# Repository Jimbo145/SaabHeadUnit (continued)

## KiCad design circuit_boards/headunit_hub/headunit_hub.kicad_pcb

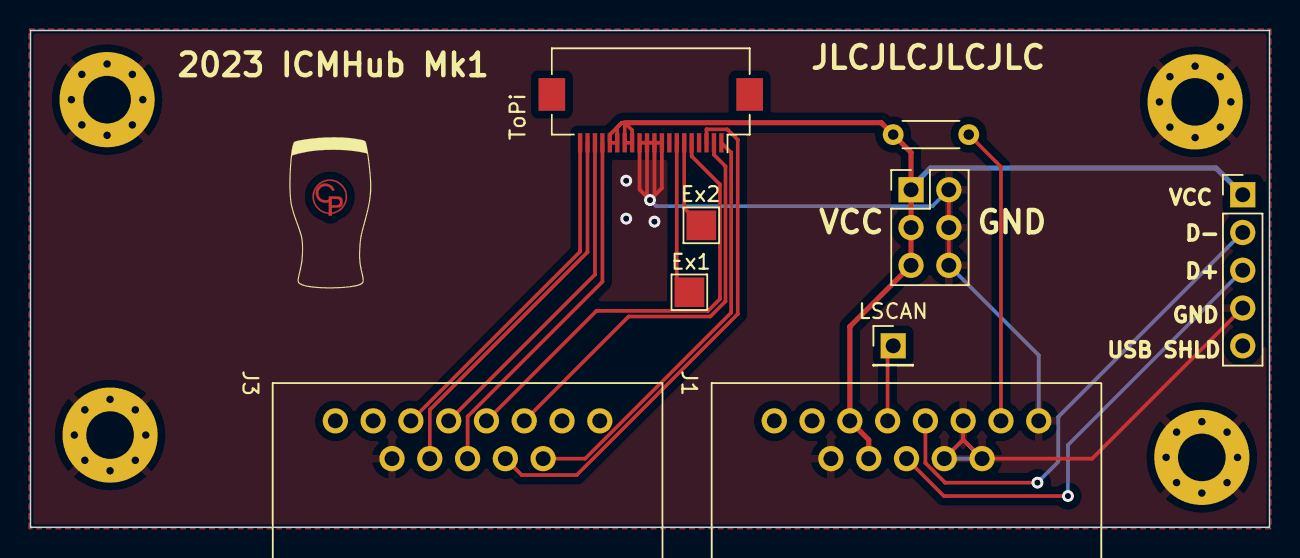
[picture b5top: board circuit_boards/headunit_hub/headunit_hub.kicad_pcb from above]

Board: 2 copper layers, 83.3 x 33.4 mm, 14 parts (0 on the bottom side), 16 nets.

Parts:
Ex1, Ex2: Conn_01x01_Pin; TestPoint_Pad_2.0x2.0mm
H1, H2, H4, H5: MountingHole_Pad; MountingHole_3.2mm_M3_Pad_Via
H3: Logo; CPlogo2(50)
J1, J3: 8P8C_LED_Shielded; rj45breakout
J5: USB_A; PinHeader_1x05_P2.54mm_Vertical
J6: Conn_02x03_Odd_Even; PinHeader_2x03_P2.54mm_Vertical
LSCAN: LSCAN; PinHeader_1x01_P2.54mm_Vertical
R1: R; R_Axial_DIN0204_L3.6mm_D1.6mm_P5.08mm_Horizontal
ToPi: Conn_01x20; Hirose_FH12-20S-0.5SH_1x20-1MP_P0.50mm_Horizontal

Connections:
/LSCAN: J1.6, LSCAN.1
/R_to_ActiveLED: J1.10, R1.2
AMFM_button: J3.1, ToPi.1
CD_button: J3.3, ToPi.3
Expansion_4: J3.8, ToPi.20
Expansion_5: J3.7, ToPi.19
Expansion_6: J3.6, ToPi.18
Expansion_7: J3.5, ToPi.17
GND: H1.1, H2.1, H4.1, H5.1, J1.1, J1.2, J1.3, J1.9, J1.SH, J3.SH, J5.4 (GND), J6.2, J6.4, J6.6, ToPi.9, ToPi.10, ToPi.11, ToPi.12
unnamed: Ex1.1, ToPi.7
unnamed: Ex2.1, ToPi.6
unnamed: J1.5, J5.3 (D+)
unnamed: J1.4, J5.2 (D-)
SCAN_button: J3.2, ToPi.2
Scrn_Brightness: J3.4, ToPi.5
VCC: J1.7, J1.8, J5.1 (VBUS), J6.1, J6.3, J6.5, R1.1, ToPi.13, ToPi.14, ToPi.15, ToPi.16

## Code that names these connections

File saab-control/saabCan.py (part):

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class GPIOManager:
    def __init__(self):
        self.pin_mapping = {
            'AMFM': gpiozero.DigitalOutputDevice(pin= 'GPIO26', active_high=True, initial_value=False),
            'SCAN': gpiozero.DigitalOutputDevice(pin= 'GPIO21', active_high=True, initial_value=False),
            'CD': gpiozero.DigitalOutputDevice(pin= 'GPIO20', active_high=True, initial_value=False),
            'scrn_brightness': gpiozero.PWMOutputDevice(pin= 'GPIO13', active_high=True, initial_value=0),
        }

    def set_gpio(self, gpio_pin: str, status: bool):
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
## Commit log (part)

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2021-05-27 Initial commit native pigpio control
2021-05-27 Update Git Ignore
2021-05-30 Somewhat working SDL package
2023-01-27 Initial commit of saab-control python scripts
2023-01-30 Add installation script and service
2023-02-11 changes to name structure and python location
2023-02-15 Update file paths
2023-03-05 Update file paths add turn signal logic
2023-03-06 Add pyzmq import
2023-03-07 Change Service script location
2023-03-07 Change Service script location (#2)
2023-03-13 Remove gitpython
2023-03-13 Dev (#3)
    * Change Service script location
    * Remove gitpython
    ---------
2023-03-14 Attempt to move Fog light on and aux change to updater.
2023-03-14 Dev (#4)
    * Change Service script location
    * Remove gitpython
    * Attempt to move Fog light on and aux change to updater.
    ---------
2023-03-14 Change Updater to run in a standalone service
2023-03-14 Dev (#5)
    * Change Service script location
    * Remove gitpython
    * Attempt to move Fog light on and aux change to updater.
    * Change Updater to run in a standalone service
    * Change Updater to run in a standalone service
    ---------
2023-03-14 Modify service files so they point to right path and are executed in order
2023-03-14 Dev (#6)
    * Change Service script location
    * Remove gitpython
    * Attempt to move Fog light on and aux change to updater.
    * Change Updater to run in a standalone service
    * Change Updater to run in a standalone service
    * Modify service files so they point to right path and are executed in order
2023-03-14 Dev (#7)
    * Change Service script location
    * Remove gitpython
    * Attempt to move Fog light on and aux change to updater.
    * Change Updater to run in a standalone service
    * Change Updater to run in a standalone service
    * Modify service files so they point to right path and are executed in order
2023-03-14 modify install.sh to work if already installed. Move After key in saab.service
2023-03-14 Dev (#8)
    * Change Service script location
    * Remove gitpython
    * Attempt to move Fog light on and aux change to updater.
    * Change Updater to run in a standalone service
    * Change Updater to run in a standalone service
    * Modify service files so they point to right path and are executed in order
2023-03-14 modify radio change messages, move foglight on back to saabCan.py
2023-03-14 Dev (#9)
    * Change Service script location
    * Remove gitpython
    * Attempt to move Fog light on and aux change to updater.
    * Change Updater to run in a standalone service
    * Change Updater to run in a standalone service
    * Modify service files so they point to right path and are executed in order
2023-03-15 Change copy command to bash
2023-03-15 Dev (#10)
    * Change Service script location
    * Remove gitpython
    * Attempt to move Fog light on and aux change to updater.
    * Change Updater to run in a standalone service
    * Change Updater to run in a standalone service
    * Modify service files so they point to right path and are executed in order
2023-03-20 remove attempt at automatic radio change. change back to get pull
2023-03-20 Dev (#11)
    * Change Service script location
    * Remove gitpython
    * Attempt to move Fog light on and aux change to updater.
    * Change Updater to run in a standalone service
    * Change Updater to run in a standalone service
    * Modify service files so they point to right path and are executed in order
2023-03-21 Update to updater to only update when updates are required
2023-03-21 Update to updater to only update when updates are required (#12)
2023-03-28 import os and remove unnecessary requirements for saab.service
2023-03-28 Updater refresh (#13)
    * Update to updater to only update when updates are required
    * import os and remove unnecessary requirements for saab.service
    ---------
2023-03-31 add api (currently commented out). add journalctl logging add automatic source changing
2023-03-31 Dev (#14)
    * Change Service script location
    * Remove gitpython
    * Attempt to move Fog light on and aux change to updater.
    * Change Updater to run in a standalone service
    * Change Updater to run in a standalone service
    * Modify service files so they point to right path and are executed in order
2023-04-05 Add Async to get_battery_status and extend install.sh
2023-04-06 Dev (#15)
    * Change Service script location
    * Remove gitpython
    * Attempt to move Fog light on and aux change to updater.
    * Change Updater to run in a standalone service
    * Change Updater to run in a standalone service
    * Modify service files so they point to right path and are executed in order
2023-04-10 add requirements.txt change systemd journal handling
2023-04-10 Dev (#16)
    * Change Service script location
    * Remove gitpython
    * Attempt to move Fog light on and aux change to updater.
    * Change Updater to run in a standalone service
    * Change Updater to run in a standalone service
    * Modify service files so they point to right path and are executed in order
2023-04-12 Update updater
2023-04-12 Dev (#17)
    * Change Service script location
    * Remove gitpython
    * Attempt to move Fog light on and aux change to updater.
    * Change Updater to run in a standalone service
    * Change Updater to run in a standalone service
    * Modify service files so they point to right path and are executed in order
2023-04-12 Start updater sooner, and stop if an update is necessary.
2023-04-12 Start updater sooner, and stop if an update is necessary. (#18)
2023-04-14 Bug Fix: use systemd-python rather than systemd
2023-04-14 Bug Fix: use systemd-python rather than systemd (#19)
2023-04-14 Bug Fix: add back can configuration, add await to copy_files
2023-04-14 Bug Fix: add back can configuration, add await to copy_files (#20)
2023-04-14 Create python-app.yml (#21)
2023-04-15 Fix saab.service script path. Add absolute path to requirements.txt for installer
2023-04-15 Fix saab.service script path. Add absolute path to requirements.txt for installer (#22)
2023-04-15 logger changes, call ip link up as sudo
2023-04-15 logger changes, call ip link up as sudo (#23)
2023-04-15 fix duplicate bracket
2023-04-15 fix duplicate bracket (#24)
2023-04-15 Change saab_update to graphical.target
2023-04-15 Change saab_update to graphical.target (#25)
2023-04-16 logging changes, fix message not sending until receive
2023-04-16 Dev (#26)
    * Change saab_update to graphical.target
    * logging changes, fix message not sending until receive
    ---------
2023-04-18 Feature: Add Auto-restart to saab.service
2023-04-18 Feature: Add Auto-restart to saab.service (#27)
2023-04-22 Add wait condition for pynput to prevent saabCan from failing if Xorg is not yet available
2023-04-22 Add wait condition for pynput to prevent saabCan from failing if Xorg is not yet available (#28)
2023-04-22 Fix source change button send, change log levels
2023-04-22 Fix source change button send, change log levels (#29)
2023-04-22 Fix source change button send, change log levels (#30)
2023-04-23 Fix update check, again change logging
2023-04-23 Fix update check, again change logging (#31)
2023-04-24 Bug fix: increase source change delay Feature: Additional logging support
2023-04-24 Bug fix: increase source change delay (#32)
    Feature: Additional logging support
2023-04-25 Cleanup repo and add documentation
2023-04-25 Cleanup repo and add documentation (#33)
2023-04-25 Feature: Add Additional Can Message Support
2023-04-25 Feature: Add Additional Can Message Support (#34)
2023-04-27 Add preliminary support for more can ids. Fix NXT button support
2023-04-28 Add preliminary support for more can ids.
2023-04-28 Adjust update
2023-04-28 Adjust update (#35)
2023-04-28 BugFix: Turn signal global variables not defined until 290 message received Feature: Added 0x143 and 0x144 canid support (windshield wipers) Change: Change 0x180 and 0x183 (Parking sensor) log messag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
2023-05-01 BugFix: Turn signal global variables not defined until 290 message received (#36)
    Feature: Added 0x143 and 0x144 canid support (windshield wipers)
    Change: Change 0x180 and 0x183 (Parking sensor) log message level
2023-05-03 Bug Fix: Turn signal handle direction Bug Fix: Fix Right turn signal timer Feature: Added Update Rev to update file
2023-05-03 Bug Fix: Turn signal handle direction (#37)
    Bug Fix: Fix Right turn signal timer
    Feature: Added Update Rev to update file
2024-02-10 Modified Kicad Files
2024-02-10 BugFix: Turn signal euro flash always active
2024-02-10 Dev (#38)
    * BugFix: Turn signal global variables not defined until 290 message received
    Feature: Added 0x143 and 0x144 canid support (windshield wipers)
    Change: Change 0x180 and 0x183 (Parking sensor) log message level
    * Modified Kicad Files
    * BugFix: Turn signal euro flash always active
    ---------
2024-02-12 Dev (#39)
    * BugFix: Turn signal global variables not defined until 290 message received
    Feature: Added 0x143 and 0x144 canid support (windshield wipers)
    Change: Change 0x180 and 0x183 (Parking sensor) log message level
    * Bug Fix: Turn signal handle direction
    Bug Fix: Fix Right turn signal timer
    Feature: Added Update Rev to update file
2024-02-13 Bug Fix: intialize Keypressed Bug Fix: turn sigal last state fix
2024-02-13 Dev (#40)
    * BugFix: Turn signal global variables not defined until 290 message received
    Feature: Added 0x143 and 0x144 canid support (windshield wipers)
    Change: Change 0x180 and 0x183 (Parking sensor) log message level
    * Bug Fix: Turn signal handle direction
    Bug Fix: Fix Right turn signal timer
    Feature: Added Update Rev to update file
2024-02-13 Bug Fix: Expose debugging website to wlan
2024-02-13 Dev (#41)
    * Bug Fix: Expose debugging website to wlan
    ---------
2024-06-21 Add devcontainer
2024-06-21 Add gitattributes
2024-06-21 Add dockerfile back
2024-06-21 Try to fix line-endings
2024-06-21 Git attributes
2024-06-21 Add ca certs to dockerfile
2024-07-26 Add webserver and improve testing capability
2024-08-05 add libs ciruit_boards
2024-08-22 Add webserver logic with websocket connection
